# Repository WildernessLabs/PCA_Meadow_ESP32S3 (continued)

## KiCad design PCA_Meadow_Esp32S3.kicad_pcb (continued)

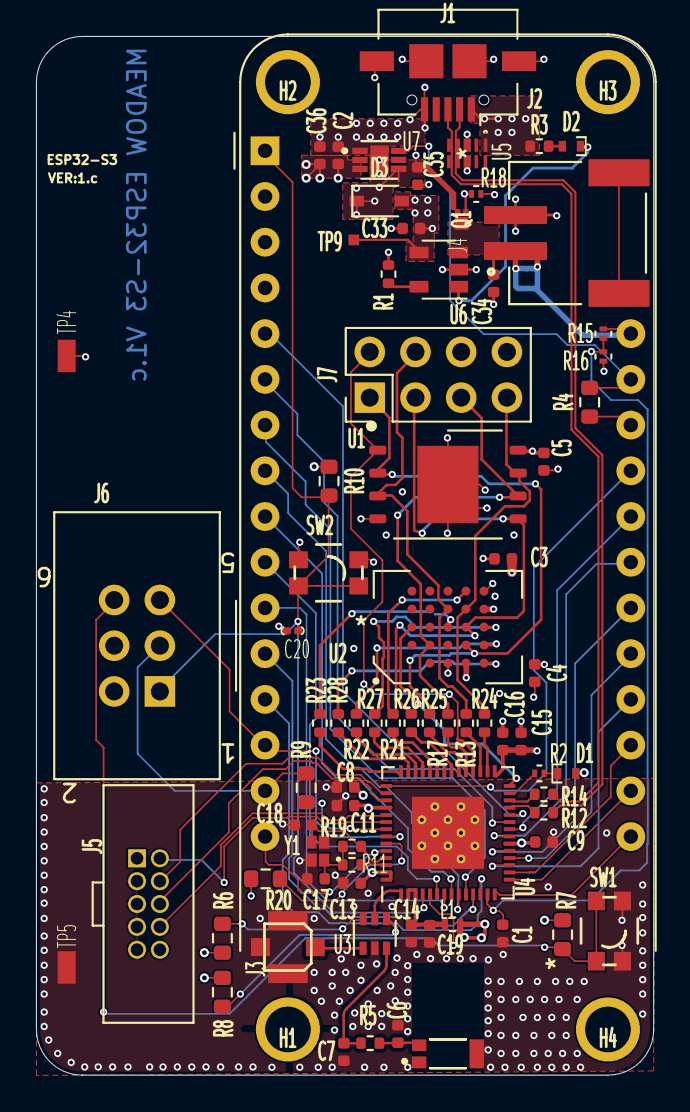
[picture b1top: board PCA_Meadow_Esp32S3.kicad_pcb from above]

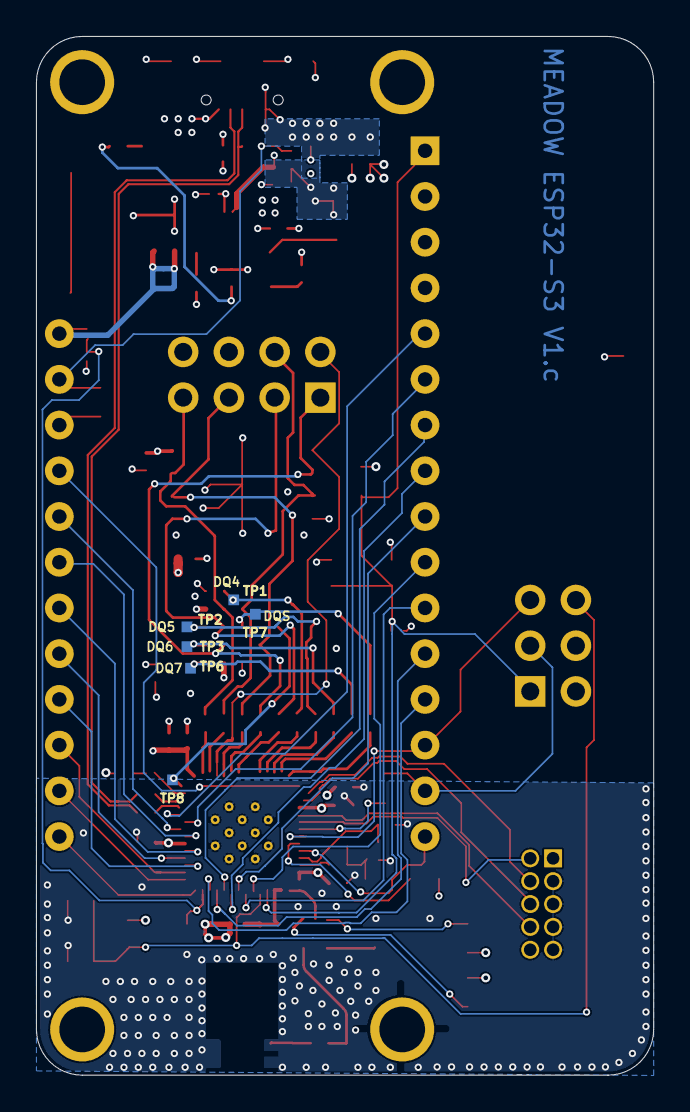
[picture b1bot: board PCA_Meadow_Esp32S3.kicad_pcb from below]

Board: 4 copper layers, 34.3 x 57.7 mm, 86 parts (6 on the bottom side), 78 nets.

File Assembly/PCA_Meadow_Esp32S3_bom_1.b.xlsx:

Component | Quantity Per PCB | References | DNI | PN | MF | PN2 | MF2 | Part | Description | Value | Footprint
1 | 1 | ANT1 |  | W3008C | PulseLarsen Antennas |  |  | W3008C | 2.4GHz Bluetooth Chip RF Antenna 2.4GHz ~ 2.483GHz 1.7dBi Solder Surface Mount | W3008C | ANTENNA_W3008C
2 | 1 | C20 |  | GRM033R60J474KE90D | Murata Electronics North America | CL03A474KQ3NNNH | Samsung Electro-Mechanics | C_0201_0.47UF_6.3V_X5R | 0.47µF ±10% 6.3V Ceramic Capacitor X5R 0201 (0603 Metric) | C_0201_0.47UF_6.3V_X5R | C_0201
3 | 1 | C13 |  | CGA2B3X5R1H223K050BB | TDK Corp |  |  | C_0402_0.022UF_50V_X5R | CAP CER 0.022UF 50V X5R 0402 | C_0402_0.022UF_50V_X5R | C_0402_1005Metric
4 | 8 | C1 C2 C3 C5 C9 C11 C14 C16 |  | C0402C104M8PACTU | KEMET | CL05A104MP5NNNC | Samsung Electro-Mechanics | C_0402_0.1UF_10V_X5R | CAP CER 0.1UF 10V X5R 0402 | C_0402_0.1UF_10V_X5R | C_0402_1005Metric
5 | 4 | C4 C19 C35 C36 |  | CL05A106MP5NUNC | Samsung Electro-Mechanics | CL05A106MP8NUB8 | Samsung Electro-Mechanics | C_0402_10UF_10V_X5R | 10µF ±20% 10V Ceramic Capacitor X5R 0402 (1005 Metric) | C_0402_10UF_10V_X5R | C_0402_1005Metric
6 | 2 | C17 C18 |  | HMK105CG120JV-F | Taiyo Yuden | GCQ1555C1H120JB01D | Murata | C_0402_12pF_50V_X5R | CAP CER 12PF 100V C0G 0402 | C_0402_12pF_50V_X5R | C_0402_1005Metric
7 | 3 | C8 C10 C15 |  | CC0402MRX5R6BB105 | Yageo | C0402C105M8PACTU | KEMET | C_0402_1UF_10V_X5R | CAP CER 1UF 10V X5R 0402 | C_0402_1UF_10V_X5R | C_0402_1005Metric
8 | 2 | C33 C34 |  | CL05A475KQ5NRNC | Samsung Electro-Mechanics | CC0402KRX5R5BB475 | Yageo | C_0402_4.7UF_10V_X5R_10% | CAP CER 4.7UF 6.3V X5R 0402 | C_0402_4.7UF_10V_X5R_10% | C_0402_1005Metric
9 | 2 | C6 C7 | DNI | CC0402CRNPO9BN8R0 | Yageo | GJM1555C1H8R0CB01D | Murata | C_0402_8pF_50V_X5R | CAP CER 8PF 50V C0G/NP0 0402 | C_0402_8pF_50V_X5R | C_0402_1005Metric
10 | 1 | D3 |  | BAT60AE6327HTSA1 | Infineon Technologies |  |  | BAT60A | Diode Schottky 10V 3A (DC) Surface Mount PG-SOD323-2 | BAT60A | D_SOD-323
11 | 1 | D1 |  | IN-S42BT5A | Inolux |  |  | LED_A_IN-S42BT5A | LED AMBER CLEAR 0402 | LED_A_IN-S42BT5A | LED_0402
12 | 1 | D2 |  | QBLP595-O | QT Brightek (QTB) |  |  | LED_O_QBLP595-O | Orange 605nm LED Indication - Discrete 2V 0402 (1005 Metric) | LED_O_QBLP595-O | LED_0402
13 | 4 | H1 H2 H3 H4 |  |  |  |  |  | MTGP356H254 | 3.56mm(0.14") pad 2.54MM(0.1") hole | MTGP356H254 | MTGP356H254
14 | 1 | J3 |  | A-1JB | Amphenol RF Division |  |  | A-1JB | U.FL (UMCC), AMC Connector Jack, Male Pin 50Ohm Surface Mount Solder | A-1JB | AMPHENOL_A-1JB
15 | 1 | J6 |  | 75869-131LF | Amphenol |  |  | AMP_02x03_75869-131LF | Connector Header Through Hole 6 position 0.100" (2.54mm) | AMP_02x03_75869-131LF | Amphenol_75869-131LF
16 | 1 | J5 |  | 3220-10-0100-00 | CNC |  |  | CNC-3220-10-0100-00 | CONN HEADER VERT 10POS 1.27MM KEY SHROADED | CNC-3220-10-0100-00 | CNC_3220-10-0100-00
17 | 1 | J1 |  | Meadow S3 Micro | Wilderness Labs |  |  | Esp32-s3Meadow | micro development kit ESP32-S3 | Esp32-s3Meadow | WL_S3_MicroMeadow
18 | 1 | J4 |  | S2B-PH-SM4-TB(LF)(SN) | JST |  |  | S2B-PH-SM4-TB(LF)(SN) | Connector Header Surface Mount, Right Angle 2 position 0.059" (1.50mm) | S2B-PH-SM4-TB(LF)(SN) | JST_S2B-PH-SM4-TB(LF)(SN)
19 | 1 | J2 |  | UJ2-MIBH-G-SMT-TR | CUI Devices |  |  | USB_B_MicroCUI | USB Micro Type B connector | USB_B_MicroCUI | USB_Micro-B_CUI_UJ2-MIBH-G
20 | 1 | L1 |  | MHQ1005P2N0CT000 | TDK Corporation |  |  | L_0402_2nH_50mΩ | FIXED IND 2NH 1A 50 MOHM SMD 1A | L_0402_2nH_50mΩ | L_0402
21 | 1 | Q1 |  | SSM3J46CTB(TPL3) | Toshiba Semiconductor and Storage |  |  | P-CH_SSM3J46CTB | P-Channel 20V 2A (Ta) Surface Mount CST3B | P-CH_SSM3J46CTB | CST3b_TOS
22 | 1 | R6 |  | RC0603JR-070RL | Yageo | ERJ-3GEY0R00V | Panasonic | R_0R_1%_0603 | RES SMD 0 OHM JUMPER 1/10W 0603 | R_0R_1%_0603 | R_0603
23 | 1 | R8 | DNI | RC0603JR-070RL | Yageo | ERJ-3GEY0R00V | Panasonic | R_0R_1%_0603 | RES SMD 0 OHM JUMPER 1/10W 0603 | R_0R_1%_0603 | R_0603
24 | 4 | R5 R11 R12 R14 |  | RMCF0402ZT0R00 | Stackpole Electronics Inc | CRCW04020000Z0ED | Vishay Dale | R_0_1%_0402 | RES 0 OHM JUMPER 1/16W 0402 | R_0_1%_0402 | R_0402_1005Metric
25 | 1 | R18 |  | RC0201FR-0710KL | Yageo |  |  | R_10K_1%_0201 | 10 kOhms ±1% 0.05W, 1/20W Chip Resistor 0201 (0603 Metric) Thick Film | R_10K_1%_0201 | R_0201
26 | 4 | R4 R7 R10 R20 |  | RC0603FR-0710KL | Yageo | RNCP0603FTD10K0 | Stackpole | R_10k_1%_0603 | RES SMD 10K OHM 1% 1/10W 0603 | R_10k_1%_0603 | R_0603
27 | 1 | R3 |  | RC0402FR-071KL | Yageo | CRCW04021K00FKEDC | Vishay Dale | R_1K_1%_0402 | RES 1K OHM 1% 1/16W 0402 | R_1K_1%_0402 | R_0402_1005Metric
28 | 1 | R19 | DNI | ERJ-2RKF1004X | Panasonic Electronic Components | RMCF0402FT1M00 | Stackpole Electronics Inc | R_1M_1%_0402 | RES SMD 1M OHM 1% 1/10W 0402 | R_1M_1%_0402 | R_0402_1005Metric
29 | 10 | R13 R17 R21 R22 R23 R24 R25 R26 R27 R28 |  | RMCF0402FT20R0 | Stackpole Electronics Inc | CRCW040220R0FKEDC | Vishay Dale | R_20_1%_0402 | RES 20 OHM 1% 1/16W 0402 | R_20_1%_0402 | R_0402_1005Metric
30 | 2 | R15 R16 |  | RC0201FR-07499KL | Yageo | ERJ-1GNF4993C | Panasonic Electronic Components | R_499K_1%_0201 | 499 kOhms ±1% 0.05W, 1/20W Chip Resistor 0201 (0603 Metric) Automotive AEC-Q200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 | R_499K_1%_0201 | R_0201
31 | 1 | R9 |  | RMCF0603FT499R | Stackpole Electronics Inc | RC0603FR-07499RL | Yageo | R_499R_1%_0603 | RES 499 OHM 1% 1/10W 0603 | R_499R_1%_0603 | R_0603
32 | 1 | R1 |  | RC0402FR-074K7L | Yageo | RMCF0402FT4K70 | Stackpole Electronics Inc | R_4K7_1%_0402 | RES 4.7K OHM 1% 1/16W 0402 | R_4K7_1%_0402 | R_0402_1005Metric
33 | 1 | R2 |  | RC0201FR-07620RL | Yageo | ERJ-1GNF6200C | Panasonic Electronic Components | R_620_1%_0201 | 620 Ohms ±1% 0.05W, 1/20W Chip Resistor 0201 (0603 Metric) Thick Film | R_620_1%_0201 | R_0201
34 | 2 | SW1 SW2 |  | 434153017835 | Würth Elektronik |  |  | SW_434153017835 | SWITCH TACTILE SPST-NO 0.05A 12V | SW_434153017835 | WURTH_434153017835
35 | 7 | TP1 TP2 TP3 TP6 TP7 TP8 TP9 | DNI |  |  |  |  | PAD_0.6X0.6MM | PAD 0.6MM X 0.6MM | PAD_0.6X0.6MM | PAD_SQ_0.6X0.6MM
36 | 2 | TP4 TP5 | DNI |  |  |  |  | TestPoint_SMT_loop_1X1.8MM | PC TEST POINT NATURAL LOOP | TestPoint_SMT_loop_1X1.8MM | TP_S2761-46R
37 | 1 | U2 |  | APS25608N-OBR-BD | AP memory |  |  | APS25608N | PSRAM 256K OCTAL SPI | APS25608N | BGA24C100P5X5_800X600X120N
38 | 1 | U5 |  | D5V0FS4U10LP-7 | Diodes Incorporated |  |  | D5V0FS4U10LP-7 |  | D5V0FS4U10LP-7 | U-DFN2510_1X2P5_DIO
39 | 1 | U4 |  | ESP32-S3 | Espessif |  |  | ESP32-S3 | Bluetooth, Wifi, Dual Core MCU | ESP32-S3 | QFN-56_EP_7x7_Pitch0.4mm
40 | 1 | U7 |  | LDL212PV33R | STMicroelectronics |  |  | LDL212PV33R | Linear Voltage Regulator IC Positive Fixed Output 1.2A 6-DFN (2x2) | LDL212PV33R | SON50P200X200X80-7N
41 | 1 | U6 |  | MCP73831T-2ACI/OT | Microchip Technology |  |  | MCP73831T-2A | Single cell, Li-Ion/Li-Po charge management controller, 4.20V, Open-Drain Statu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 | MCP73831T-2A | SOT-23-5
42 | 1 | U3 |  | SKYA21001 | Skyworks Solutions Inc. |  |  | SKYA21001 | RF Switch IC Bluetooth, WLAN SPDT 3GHz 50Ohm SC-70-6 | SKYA21001 | SOT-363_SC-70-6
43 | 1 | U1 |  | W25Q512NWEIM | Winbond |  |  | W25Q512NWE | SPIFLASH, 512M-BIT, 1.8V, 4KB UN | W25Q512NWE | WSON-8-1EP_6x8mm_P1.27mm_EP3.4x4.3mm
44 | 1 | Y1 |  | ABM12W-40.0000MHZ-7-B1U-T3 | Abracon LLC |  |  | ABM12W-40.0000MHZ-7-B1U-T3 | 40MHz ±10ppm Crystal 7pF 50 Ohms 4-SMD, No Lead | ABM12W-40.0000MHZ-7-B1U-T3 | XTAL_ABM12W-24.0000MHZ-6-B1U-T3
Component Groups: | 44
Component Count: | 86
Fitted Components: | 86
Number of PCBs: | 1
Total components: | 86
Schematic Version: | 1.b
Schematic Date: | 2022-02-19
PCB Variant: | [u'default']
BoM Date: | 2/19/2022 11:01:20 AM
Schematic Source: | PCA_Meadow_Esp32S3.kicad_sch
KiCad Version: | Eeschema (6.0.1-133-gaa5b6c70a7)

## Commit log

2022-01-02 Update gitignore
2022-01-02 Esp32-s3 page is mostly complete
2022-01-15 Added memory, upadated micro usb connector and page to remove extras
2022-01-15 updated git ignore for auto-save-files
2022-01-16 Added feather conenctor
2022-01-17 Preliminary placement fixed 0603 foot prints
2022-01-24 Added debug conenctors for the SPI memory bus, updated pcb outline, add 3D models for missing parts
2022-02-05 PCB: Added copper pours, USB routing, stack up. Sch: Added TVS for usb
2022-02-06 Some RAM Routed
2022-02-07 Most of the routing complete
2022-02-08 FInish layout checked DRCs, made gerbers
2022-02-08 final save
2022-02-10 Updated esp32-s3 to work with JLCPCB
2022-02-19 Added chagnes suggested by esp
2022-02-19 Added BOM to version 1.b
2022-02-19 Add placement file and edited git ignore file to use it
2022-02-21 Cleared up some notes from the vendor
2022-09-28 updated esp32s3 footprint and fixed all errors
2022-09-28 added gerbers
2022-09-28 last save
